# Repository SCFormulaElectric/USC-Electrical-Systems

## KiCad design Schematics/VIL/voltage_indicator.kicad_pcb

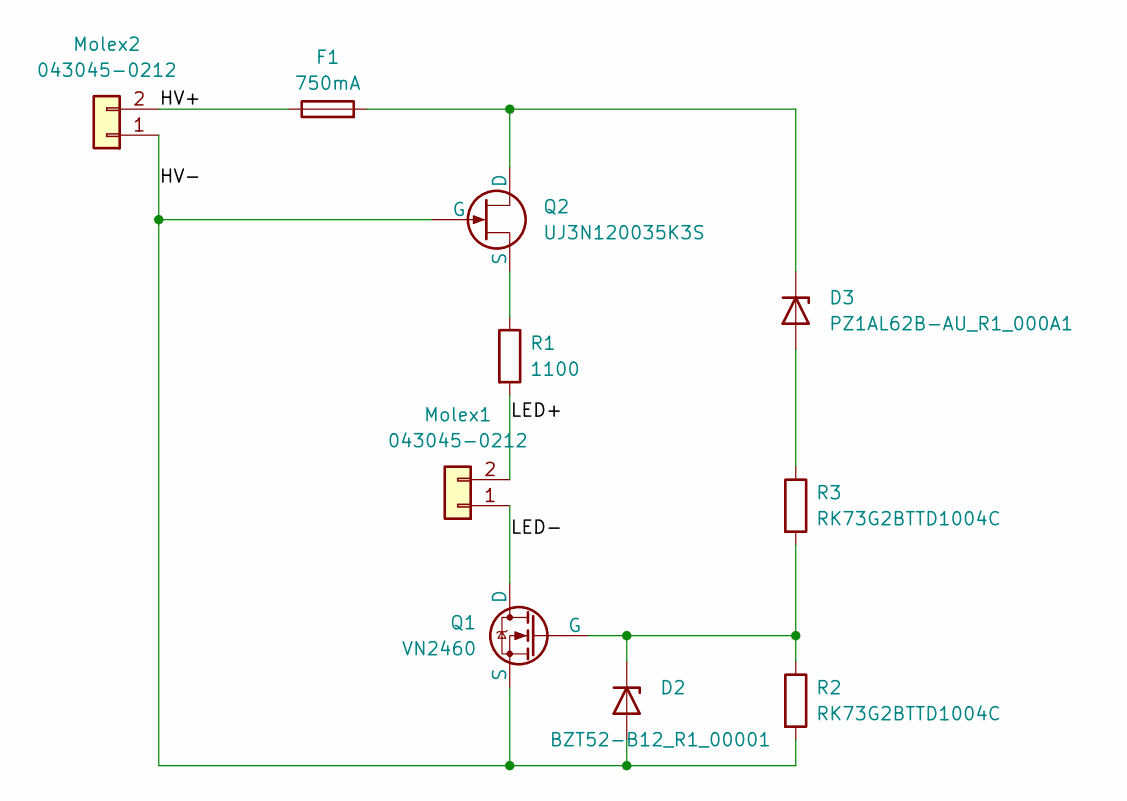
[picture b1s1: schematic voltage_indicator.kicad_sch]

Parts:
D2: BZT52-B12_R1_00001; D_SOD-123
D3: PZ1AL62B-AU_R1_000A1; D_SOD-123F
F1: 750mA; FUSE_BK_PCS
Molex1, Molex2: 043045-0212; Molex_Micro-Fit_3.0_43045-0212_2x01_P3.00mm_Vertical
Q1: VN2460; TO-92
Q2: UJ3N120035K3S; TO-247-3_Horizontal_TabDown
R1: 1100; R_Axial_DIN0207_L6.3mm_D2.5mm_P7.62mm_Horizontal
R2, R3: RK73G2BTTD1004C; RESC3116X65N

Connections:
/HV+: F1.1, Molex2.2
/HV-: D2.2 (A), Molex2.1, Q1.1 (S), Q2.1 (G), R2.2
/LED+: Molex1.2, R1.2
/LED-: Molex1.1, Q1.3 (D)
unnamed: D2.1 (K), Q1.2 (G), R2.1, R3.2
unnamed: D3.2 (A), R3.1
unnamed: D3.1 (K), F1.2, Q2.2 (D)
unnamed: Q2.3 (S), R1.1

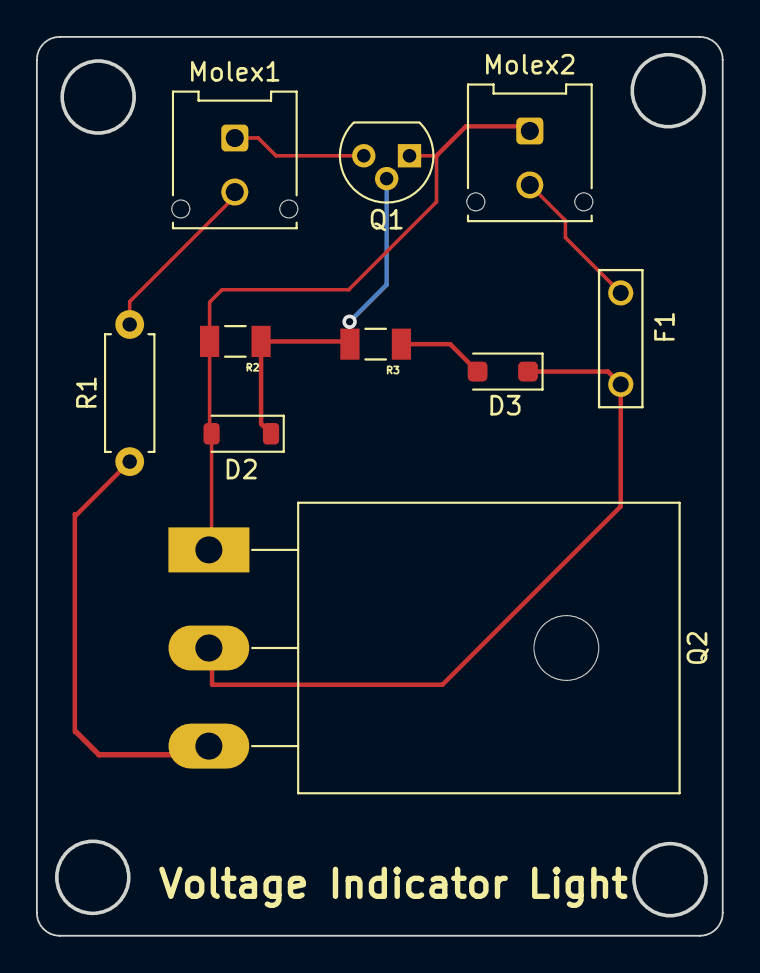
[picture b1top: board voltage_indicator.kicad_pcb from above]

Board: 2 copper layers, 38.1 x 49.9 mm, 10 parts (0 on the bottom side), 8 nets.
